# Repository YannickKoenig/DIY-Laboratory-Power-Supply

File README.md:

# DIY Laboratory Power Supply Unit
A simple, microcontroller-based PWM buck converter power supply, designed to provide precise voltage control and current measurement. The output voltage is easily adjustable using a rotary encoder for accurate and intuitive input. This project is compact, affordable, and perfect for DIY laboratory power supply applications.

## Features
- Voltage regulation via PWM buck converter
- User-friendly voltage adjustment using a rotary encoder
- Real-time display of voltage and current
- Custom PCB Boards
- Compact and cost-effective design (~9€)

## Table of Contents  
- [BOM](#bom)
- [Assembly](#assembly)  
- [Usage](#usage)  
- [Contributing](#contributing)  
- [License](#license)
- [Schematics](#schematics)

## Bill of Materials (BOM)

| Item                   | Description                         | Quantity | Price   | Total   |
|------------------------|-------------------------------------|----------|---------|---------|
| KY-040                 | Rotary Encoder                      | 1        | 0,89 €  | 0,89 €  |
| IRLZ44N                | MOSFET-Transistor (TO-220)          | 1        | 0,22 €  | 0,22 €  |
| Fuse (2A)              | 5x20mm Glass Fuse                   | 1        | 0,03 €  | 0,03 €  |
| SS34                   | Schottky Diode                      | 1        | 0,02 €  | 0,02 €  |
| TM1637                 | 4-digit 7-segment LED Display       | 2        | 1,90 €  | 3,80 €  |
| DC Plug                | -                                   | 1        | 0,24 €  | 0,24 €  |
| Power Switch           | -                                   | 1        | 0,12 €  | 0,12 €  |
| TC4427                 | MOSFET Driver (SOP-8)               | 1        | 0,29 €  | 0,29 €  |
| Buck Converter PCB     | Custom PCB for Buck Converter       | 1        | 0,08 €  | 0,08 €  |
| Frontend PCB (optional)| Custom PCB for Input & Displays     | 1        | 0,80 €  | 0,80 €  |
| Raspberry Pi Pico      | Microcontroller                     | 1        | 2,00 €  | 2,00 €  |
| Electrolytic Capacitor  | 470µF                               | 1        | 0,30 €  | 0,30 €  |
| Ceramic Capacitor      | 1µF                                 | 1        | 0,10 €  | 0,10 €  |
| Inductor               | CD75, 47UH                          | 1        | 0,10 €  | 0,10 €  |
| SMD Resistor           | Values 51k and 10k (1206)           | 2        | 0,01 €  | 0,02 €  |
| SMD Resistor           | Value 0.1 Ohm      (2512)           | 1        | 0,01 €  | 0,01 €  |

**Total: 9,01 €**

## Assembly
1. **Order the PCBs**:
For easier and cleaner assembly, it is recommended to order the PCBs from manufacturers like JLCPCB, PCBWAY, or AllPCB. Both the Buck Converter PCB and the optional Frontend PCB can be used. Just upload the appropriate Gerber files ([buckdown-pcb](hardware/electrical/buck-converter/Gerber), [frontend-pcb](hardware/electrical/frontend/Gerber))
2. **Solder the components**:
Carefully solder all the required components. The project includes both SMD and THT parts, so make sure you have the right tools and technique.
3. **Flash the microcontroller**:
-   Connect the Raspberry Pi Pico to your computer while holding the **BOOTSEL** button during startup.
-   You can either compile the firmware yourself or simply upload the precompiled `.uf2` file provided in the **releases** section.

4. **Connect the wiring**:
-   Connect the **Buck Converter PCB** and the **Frontend PCB** (if used) using the following connections:
    
    -   `GND` → `GND`
        
    -   `I+` → `I_in`
        
    -   `U+` → `U_in`
        
-   Connect the output of the Buck Converter:
    
    -   `V_out+` → Positive output terminal (e.g., banana plug).
        
    -   `V_out-` → Negative output terminal (e.g., banana plug).

You can use banana plugs, terminal blocks, or any other suitable connectors for your output.

-   If using the **Frontend PCB**, connect both **TM1637 displays** and the **rotary encoder** to the appropriate headers.
    
-   Make sure to add a **fuse (e.g., 2A)** to protect your circuit from potential damage.
    
-   To power the **Raspberry Pi Pico**, you can either:
    
    -   Power it via **USB**, or
        
    -   Use a separate **buck converter module** (e.g., LM2596S) connected in parallel with the DC input.

## Usage

To adjust the output voltage:

- Turn the rotary encoder **left** to decrease the selected digit.
- Turn it **right** to increase the selected digit.
- Press the rotary encoder to switch between digits.

You can fine-tune the PI controller parameters (`K_P` and `K_I`) experimentally in the firmware to improve voltage regulation stability and response. See [RegulatorManager.hpp](./software/RegulatorManager.hpp) for details.

## Contributing

Contributions are welcome! Feel free to fork this project, submit pull requests, or open issues for improvements and bug fixes.

## Third-Party Libraries

This project uses the following third-party software:

- **Raspberry Pi Pico SDK**  
  Official SDK for Raspberry Pi Pico microcontroller.  
  License: BSD 3-Clause  
  [https://github.com/raspberrypi/pico-sdk](https://github.com/raspberrypi/pico-sdk)

- **TM1637_lib**  
  Library for controlling TM1637 7-segment displays.  
  License: MIT  
  [https://github.com/gavinlyonsrepo/displaylib_LED_PICO](https://github.com/gavinlyonsrepo/displaylib_LED_PICO)

## License

This project is open-source and available under the [MIT License](LICENSE.md).

## Schematics

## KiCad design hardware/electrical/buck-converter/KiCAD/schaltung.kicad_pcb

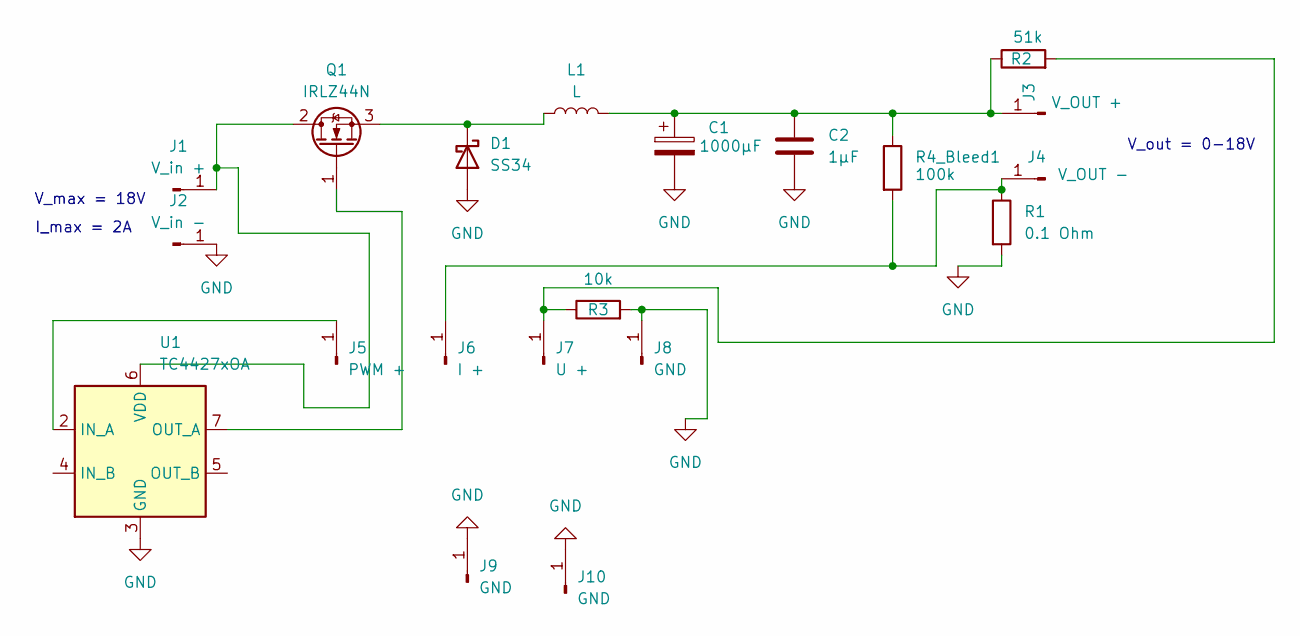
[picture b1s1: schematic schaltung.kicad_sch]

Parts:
C1: 1000µF; CP_Radial_D10.0mm_P5.00mm
C2: 1µF; C_Disc_D5.0mm_W2.5mm_P5.00mm
D1: SS34; D_SMA
J1: V_in +; MountingHole_2.2mm_M2_Pad
J2: V_in -; MountingHole_2.2mm_M2_Pad
J3: V_OUT +; MountingHole_2.2mm_M2_Pad
J4: V_OUT -; MountingHole_2.2mm_M2_Pad
J5: PWM +; MountingHole_2.2mm_M2_Pad
J6: I +; MountingHole_2.2mm_M2_Pad
J7: U +; MountingHole_2.2mm_M2_Pad
J8, J9, J10: GND; MountingHole_2.2mm_M2_Pad
L1: L; L_Sunlord_MWSA1003S
Q1: IRLZ44N; TO-220-3_Vertical
R1: 0.1 Ohm; R_2512_6332Metric
R2: 51k; R_1206_3216Metric
R3: 10k; R_1206_3216Metric
R4_Bleed1: 100k; R_1206_3216Metric
U1: TC4427xOA; SOIC-8_3.9x4.9mm_P1.27mm

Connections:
GND: C1.2, C2.2, D1.2 (A), J2.1, J8.1, J9.1, J10.1, R1.2, R3.2, U1.3 (GND)
unnamed: D1.1 (K), L1.1, Q1.3 (S)
unnamed: J1.1, Q1.2 (D), U1.6 (VDD)
unnamed: C1.1, C2.1, J3.1, L1.2, R2.1, R4_Bleed1.1
unnamed: J4.1, J6.1, R1.1, R4_Bleed1.2
unnamed: J5.1, U1.2 (IN_A)
unnamed: J7.1, R2.2, R3.1
unnamed: Q1.1 (G), U1.7 (OUT_A)

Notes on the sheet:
I_max = 2A
V_max = 18V
V_out = 0-18V

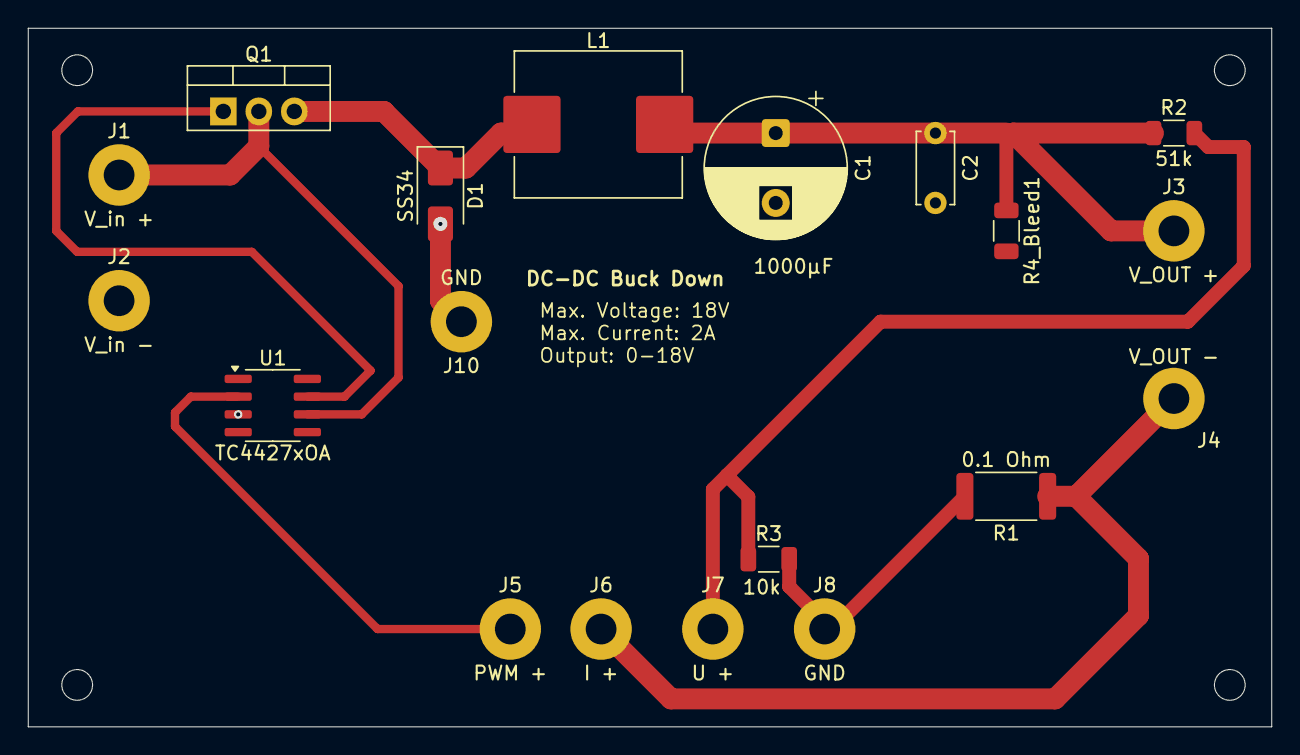
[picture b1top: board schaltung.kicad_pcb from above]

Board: 2 copper layers, 89.0 x 50.0 mm, 20 parts (0 on the bottom side), 8 nets.

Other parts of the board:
REF1: MountingHole_2.2mm_M2

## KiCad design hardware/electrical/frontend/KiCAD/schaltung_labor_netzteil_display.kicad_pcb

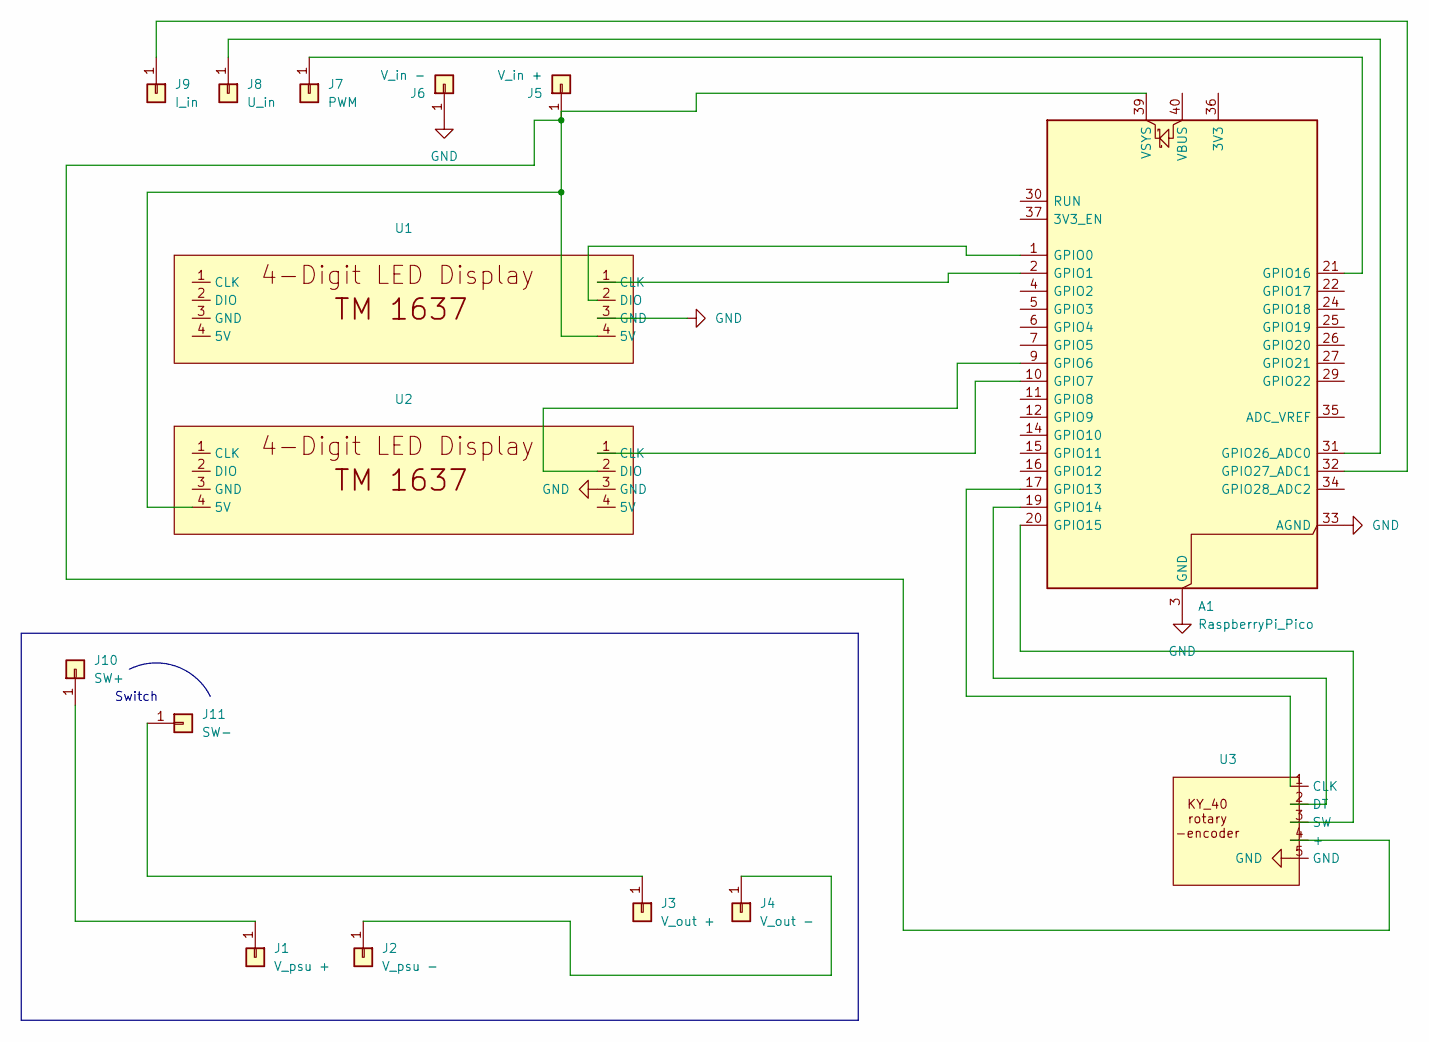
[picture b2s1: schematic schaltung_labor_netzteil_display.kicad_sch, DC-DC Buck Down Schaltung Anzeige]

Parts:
A1: RaspberryPi_Pico; RaspberryPi_Pico_Common_Unspecified
J1: V_psu +; PinSocket_1x01_P2.54mm_Vertical
J2: V_psu -; PinSocket_1x01_P2.54mm_Vertical
J3: V_out +; PinSocket_1x01_P2.54mm_Vertical
J4: V_out -; PinSocket_1x01_P2.54mm_Vertical
J5: V_in +; PinSocket_1x01_P2.54mm_Vertical
J6: V_in -; PinSocket_1x01_P2.54mm_Vertical
J7: PWM; PinSocket_1x01_P2.54mm_Vertical
J8: U_in; PinSocket_1x01_P2.54mm_Vertical
J9: I_in; PinSocket_1x01_P2.54mm_Vertical
J10: SW+; PinSocket_1x01_P2.54mm_Vertical
J11: SW-; PinSocket_1x01_P2.54mm_Vertical
U1, U2: TM1637
U3: KY_40

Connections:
GND: A1.3 (GND), A1.8 (GND), A1.13 (GND), A1.18 (GND), A1.23 (GND), A1.28 (GND), A1.33 (AGND), A1.38 (GND), J6.1, U1.3 (GND), U2.3 (GND), U3.5 (GND)
unnamed: A1.1 (GPIO0), U1.2 (DIO)
unnamed: A1.2 (GPIO1), U1.1 (CLK)
unnamed: A1.9 (GPIO6), U2.2 (DIO)
unnamed: A1.10 (GPIO7), U2.1 (CLK)
unnamed: A1.17 (GPIO13), U3.1 (CLK)
unnamed: A1.19 (GPIO14), U3.2 (DT)
unnamed: A1.20 (GPIO15), U3.3 (SW)
unnamed: A1.21 (GPIO16), J7.1
unnamed: A1.31 (GPIO26_ADC0), J8.1
unnamed: A1.32 (GPIO27_ADC1), J9.1
unnamed: A1.39 (VSYS), J5.1, U1.4 (5V), U2.4 (5V), U3.4 (+)
unnamed: J1.1, J10.1
unnamed: J2.1, J4.1
unnamed: J3.1, J11.1

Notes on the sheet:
Switch

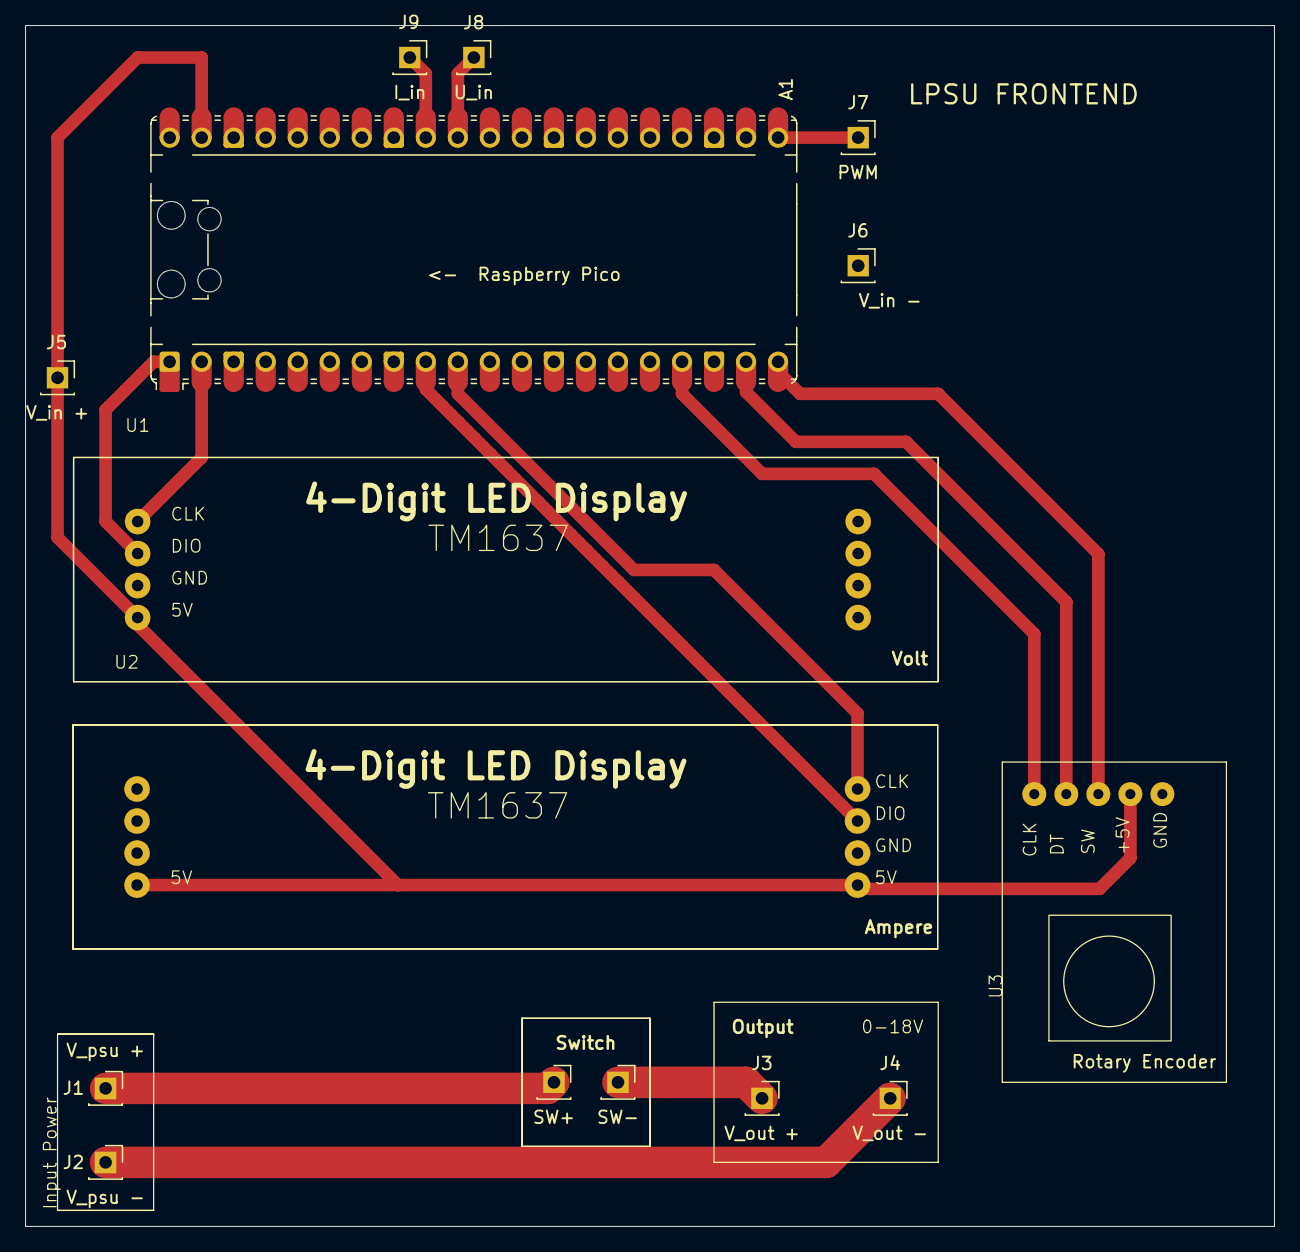
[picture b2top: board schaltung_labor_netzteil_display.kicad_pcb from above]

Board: 2 copper layers, 99.1 x 95.2 mm, 15 parts (0 on the bottom side), 15 nets.

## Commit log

2025-06-18 added readme
2025-06-18 Improved folder structure
2025-06-18 Rename 3D Render.png to 3D-Render.png
2025-06-18 Fixed gpio bug
2025-06-18 Updated images
2025-06-18 updated cover
2025-06-18 Add display example gif
2025-06-19 Update RegulatorManager.cpp
    Corrected current calculation
2025-06-19 Update RotaryEncoder.hpp, removed commend
2025-06-20 Improved system stability
2025-06-20 Improved PI-Regulation
2025-06-20 Increased Frequency
2025-06-20 Updated PCBs; added Bleed Resistor and fixed Frontend GND connections
2025-06-20 Repaired PWM frequency
